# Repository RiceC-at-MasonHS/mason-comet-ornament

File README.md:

# Mason Comet Ornament
This is a simple PCB that demonstrates the use of [KiCad](https://www.kicad.org/).
All custom shapes drawn in [Inkscape](https://inkscape.org/) vector design software.

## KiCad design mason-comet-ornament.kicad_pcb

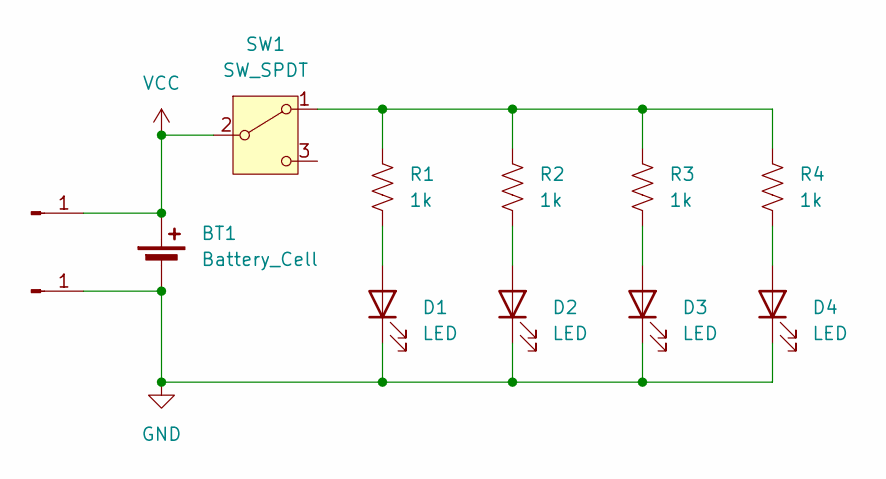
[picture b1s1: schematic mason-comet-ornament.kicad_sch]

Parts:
BT1: Battery_Cell; BatteryHolder_Multicomp_BC-2001_1x2032
D1, D2, D3, D4: LED; D_0603_1608Metric
J1, J2: Conn_01x01_Pin; PinHeader_1x01_P1.00mm_Vertical
R1, R2, R3, R4: 1k; LED_1206_3216Metric_Pad1.42x1.75mm_HandSolder
SW1: SW_SPDT; SW_SPDT_PCM12

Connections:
GND: BT1.2 (-), D1.1 (K), D2.1 (K), D3.1 (K), D4.1 (K), J2.1
unnamed: D1.2 (A), R1.2
unnamed: D2.2 (A), R2.2
unnamed: D3.2 (A), R3.2
unnamed: D4.2 (A), R4.2
unnamed: R1.1, R2.1, R3.1, R4.1, SW1.1 (A)
VCC: BT1.1 (+), J1.1, SW1.2 (B)

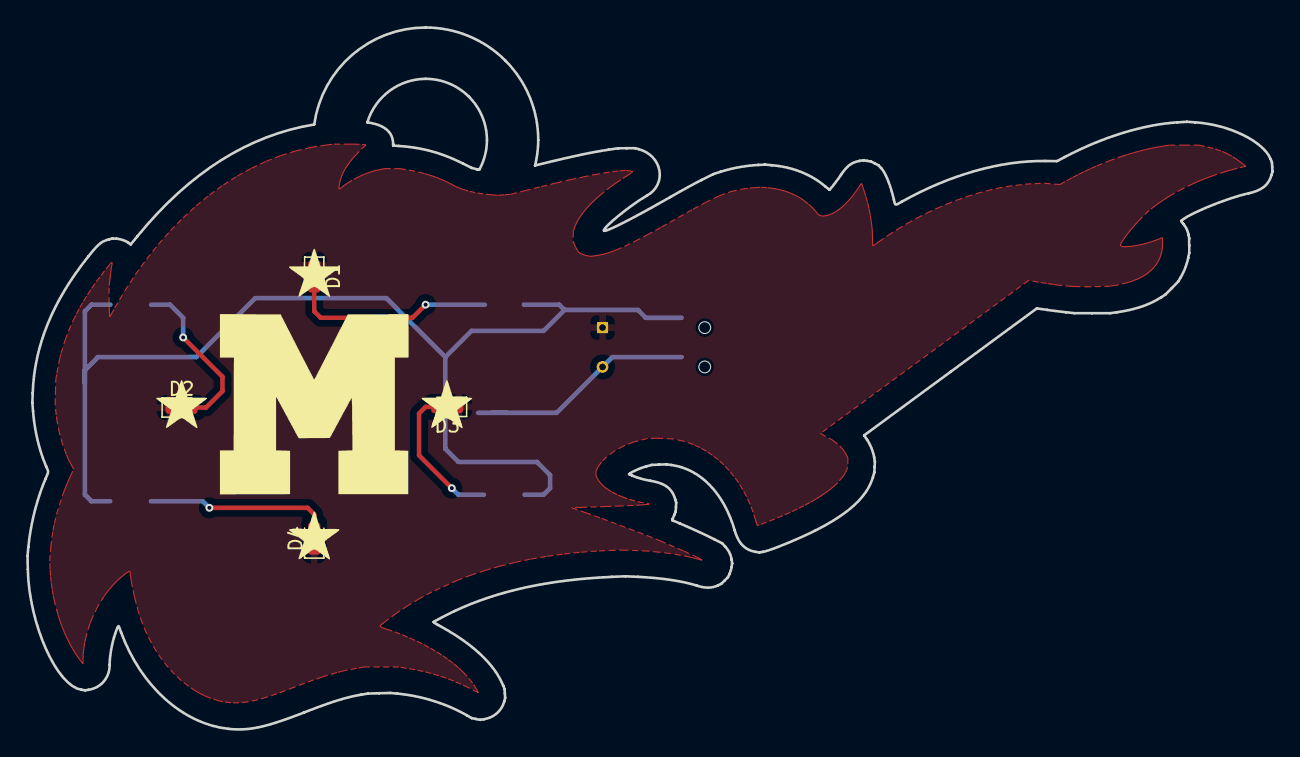
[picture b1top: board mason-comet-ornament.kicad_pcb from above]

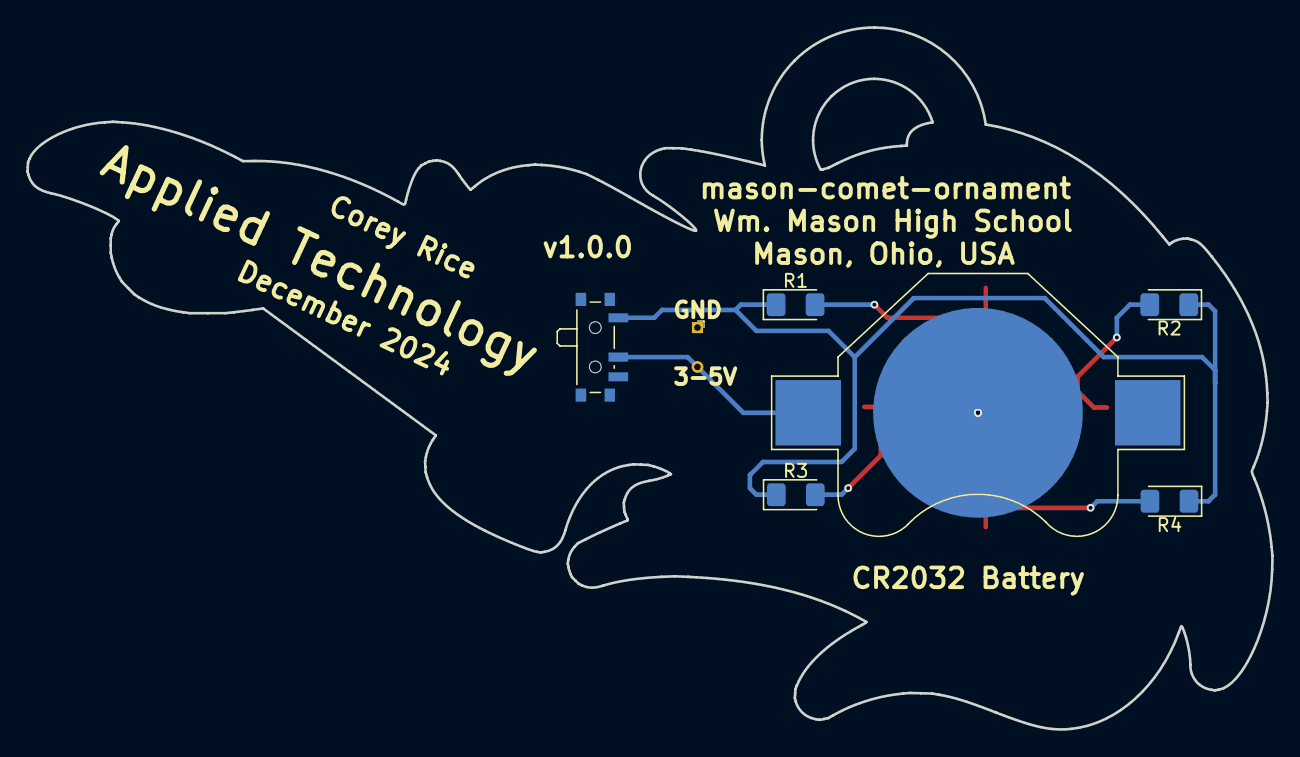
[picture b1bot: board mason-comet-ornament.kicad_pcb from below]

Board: 2 copper layers, 95.0 x 53.6 mm, 12 parts (6 on the bottom side), 7 nets.

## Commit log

2024-11-23 update project details
2024-11-24 use standard kicad gitignore
2024-11-24 Added second power access
2024-11-24 added image to readme
2024-11-26 aliged with digikey parts/ordering
2024-11-27 added gerber.zip
2024-11-27 uninterrupted stars
2024-11-27 release version
2024-11-27 gerber files
2024-11-27 updated image
2024-11-29 labeled vcc net
2024-11-29 updated sheet notes
2024-11-29 added interactive BOM
2024-11-29 rename /bom to /docs for github pages
2024-11-29 nonstandard filename did not work for GH pages: instead trying simple redirect page
2024-11-29 improved documentation
2024-12-02 (chore) remove docs page
2024-12-02 remove border on image
